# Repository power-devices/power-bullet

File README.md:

# Welcome to the Power Bullet electronics repository

I teach power electronics and I want to provide my students the best experience possible. This is the reason I created this project. I intend to allow people to produce power electronics devices at an extreme low cost. This board required 4 layers, but this is no problem today due to [JLCPCB](https://jlcpcb.com/) or other manufacturers.

So far, the project is divided into 3 pieces:

 1. Power supply: used to delivery power the other boards, it is compatible with mono-three phase up to 220 VAC
 2. Power bullet: a three phase h-bridge, simple as that
 3. Power brain F103: the main controller

# Disclaimer

I provide no warranty at all. Use it at your own risk!

# What will I find here?

You will find the design and production files. To edit the schematic/board you will need to install Kicad. I used version 7 to create this board.

# What can I do with this?

In this repository the board design and production files are stored. You are welcome to download/distribute it, use it, whatever.

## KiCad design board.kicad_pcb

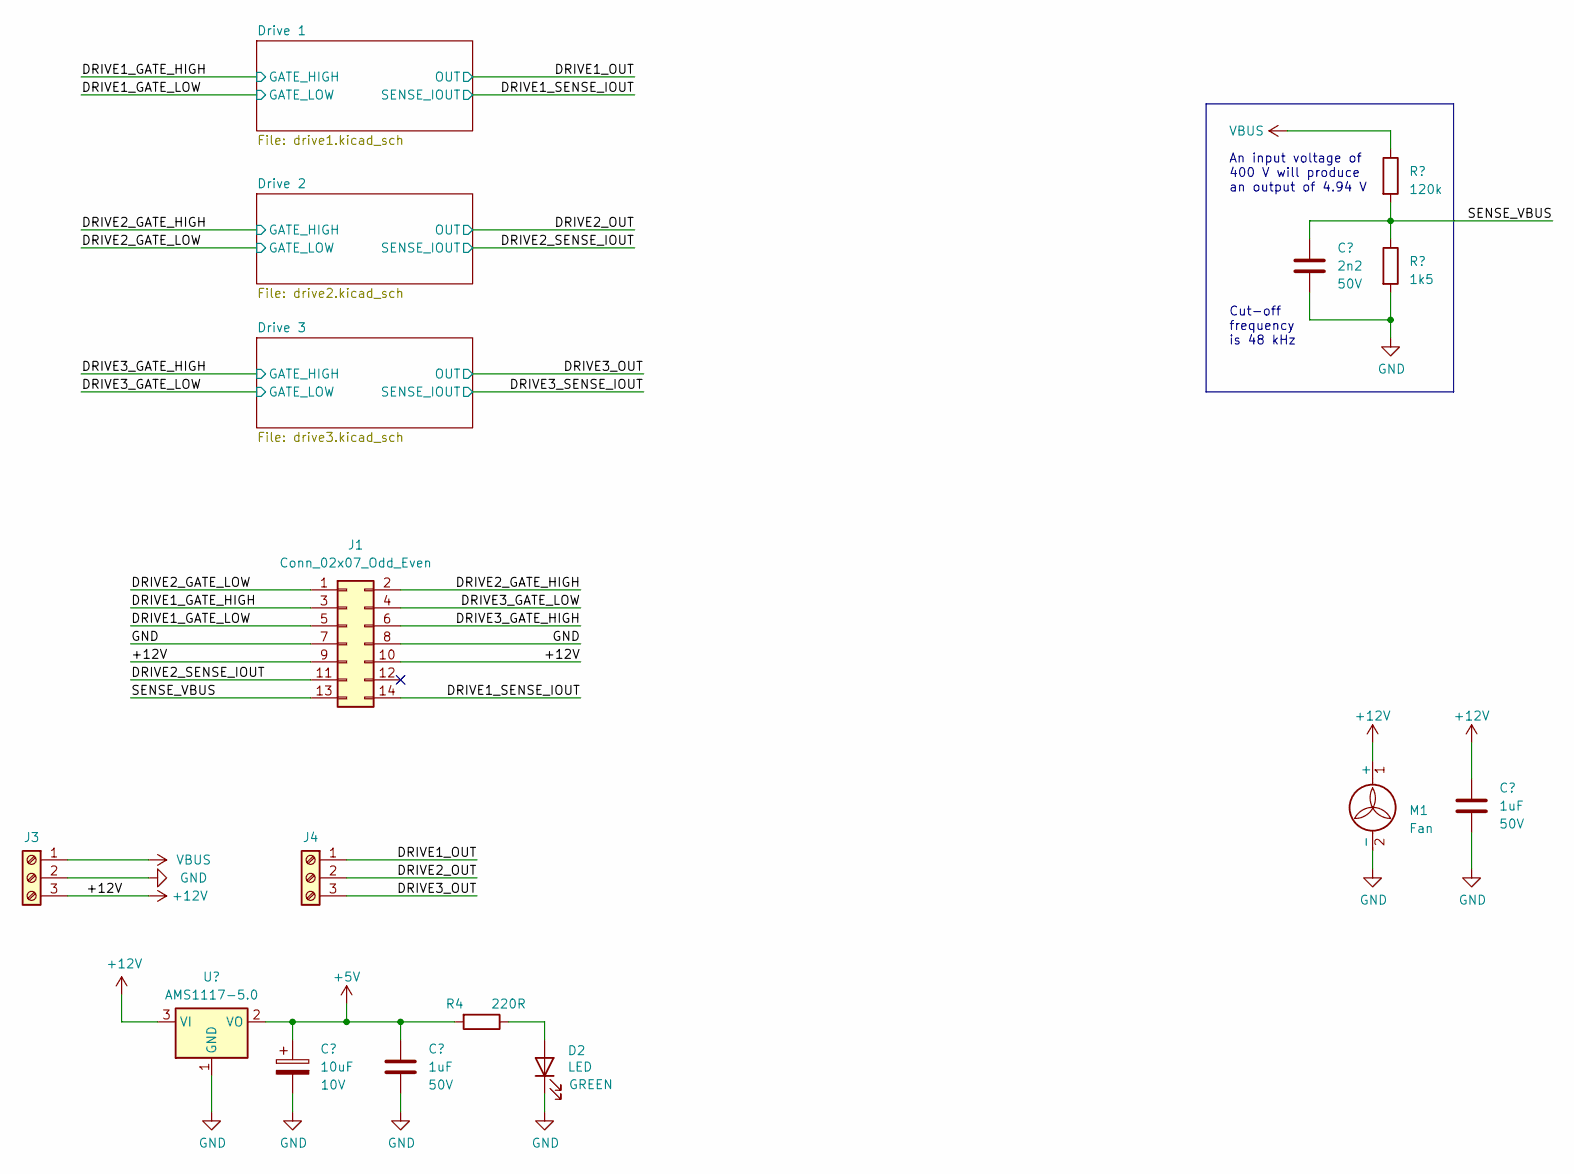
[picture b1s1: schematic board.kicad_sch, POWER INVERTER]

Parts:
C1, C5: 1uF; C_1206_3216Metric_Pad1.33x1.80mm_HandSolder; Voltage 50V
C2: 2n2; C_1206_3216Metric; Voltage 50V
C4: 10uF; CP_EIA-3216-18_Kemet-A; Voltage 10V
D2: LED; LED_1206_3216Metric_Pad1.42x1.75mm_HandSolder
J1: Conn_02x07_Odd_Even; IDC-Header_2x07_P2.54mm_Vertical
J3, J4: Screw_Terminal_01x03; TerminalBlock_Phoenix_MKDS-1,5-3_1x03_P5.00mm_Horizontal
M1: Fan; JST_XH_B2B-XH-A_1x02_P2.50mm_Vertical
R1: 120k; R_1206_3216Metric_Pad1.30x1.75mm_HandSolder
R2: 1k5; R_1206_3216Metric_Pad1.30x1.75mm_HandSolder
R4: 220R; R_1206_3216Metric_Pad1.30x1.75mm_HandSolder
U2: AMS1117-5.0; SOT-223-3_TabPin2

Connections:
+5V: C4.1, C5.1, R4.2, U2.2 (VO); also elsewhere on the board
+12V: C1.1, J1.9, J1.10, J3.3, M1.1 (+), U2.3 (VI); also elsewhere on the board
/DRIVE1_GATE_HIGH: J1.3; also elsewhere on the board
/DRIVE1_GATE_LOW: J1.5; also elsewhere on the board
/DRIVE1_OUT: J4.1; also elsewhere on the board
/DRIVE1_SENSE_IOUT: J1.14; also elsewhere on the board
/DRIVE2_GATE_HIGH: J1.2; also elsewhere on the board
/DRIVE2_GATE_LOW: J1.1; also elsewhere on the board
/DRIVE2_OUT: J4.2; also elsewhere on the board
/DRIVE2_SENSE_IOUT: J1.11; also elsewhere on the board
/DRIVE3_GATE_HIGH: J1.6; also elsewhere on the board
/DRIVE3_GATE_LOW: J1.4; also elsewhere on the board
/DRIVE3_OUT: J4.3; also elsewhere on the board
/SENSE_VBUS: C2.1, J1.13, R1.2, R2.1
GND: C1.2, C2.2, C4.2, C5.2, D2.1 (K), J1.7, J1.8, J3.2, M1.2 (-), R2.2, U2.1 (GND); also elsewhere on the board
unnamed: D2.2 (A), R4.1
VBUS: J3.1, R1.1; also elsewhere on the board

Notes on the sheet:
An input voltage of 400 V will produce an output of 4.94 V
Cut-off frequency is 48 kHz

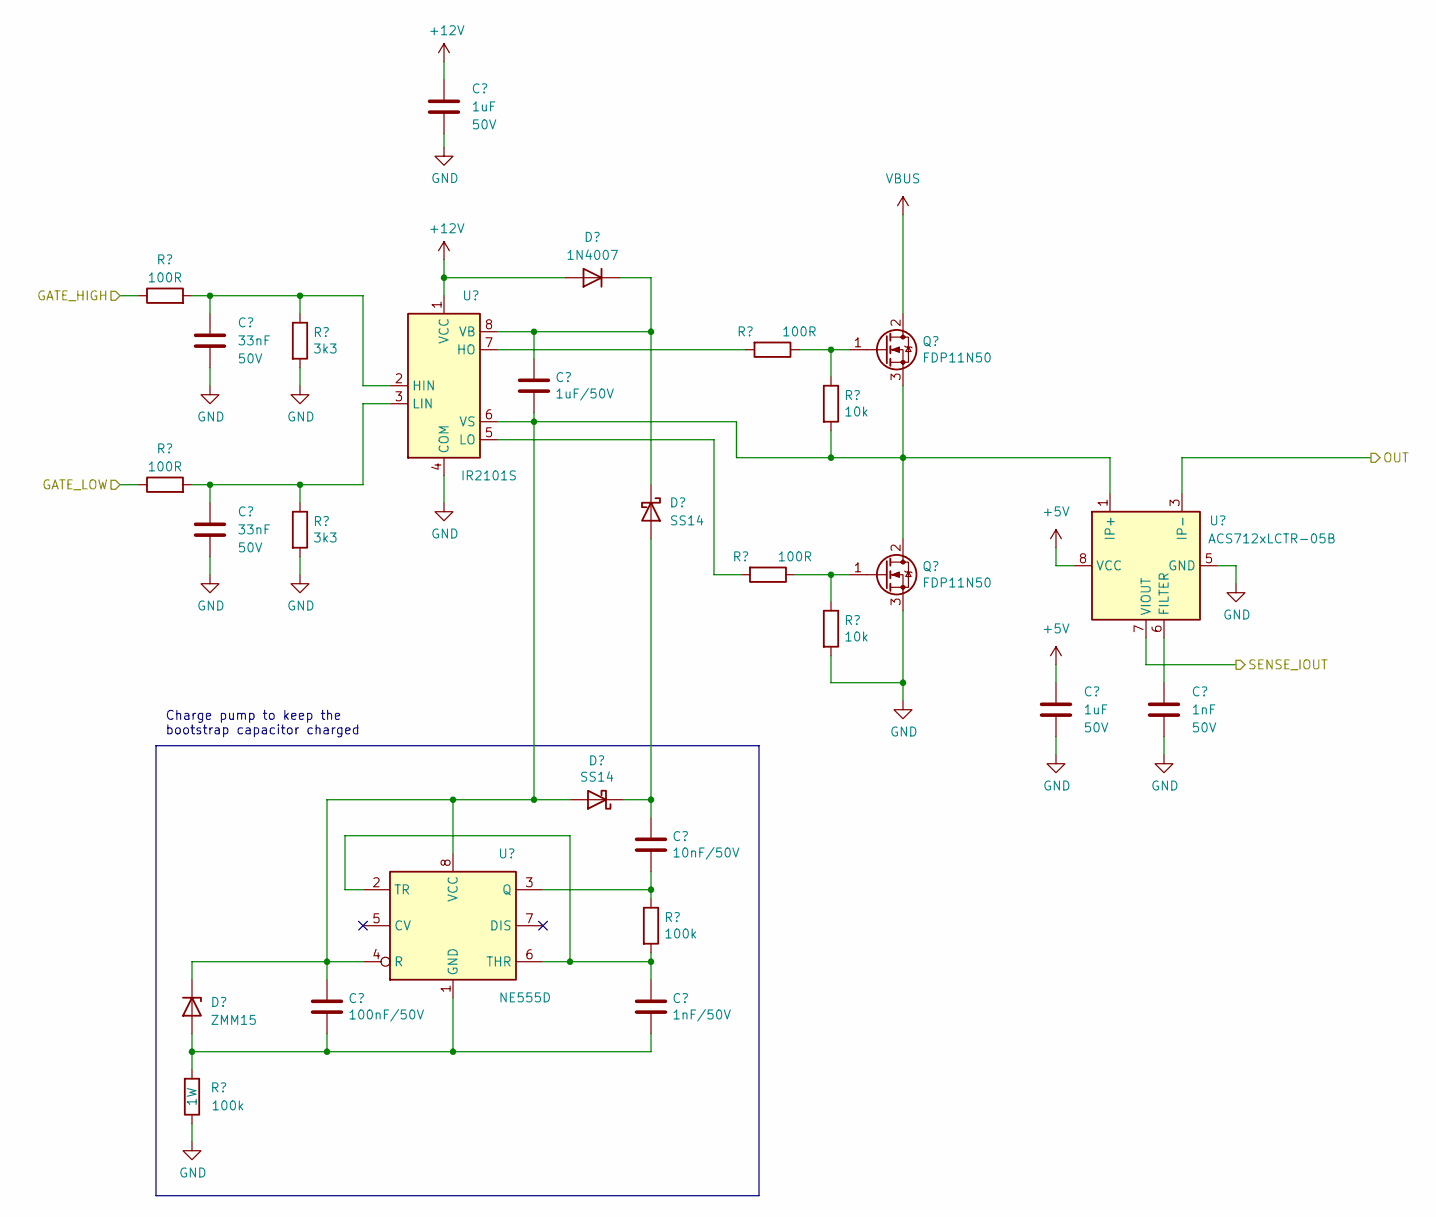
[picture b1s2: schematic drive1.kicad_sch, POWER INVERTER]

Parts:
C8, C14: 1uF; C_1206_3216Metric_Pad1.33x1.80mm_HandSolder; Voltage 50V
C10, C13: 33nF; C_1206_3216Metric; Voltage 50V
C11: 1uF/50V; C_1206_3216Metric_Pad1.33x1.80mm_HandSolder
C15: 1nF; C_1206_3216Metric_Pad1.33x1.80mm_HandSolder; Voltage 50V
C17: 10nF/50V; C_1206_3216Metric_Pad1.33x1.80mm_HandSolder
C18: 100nF/50V; C_1206_3216Metric_Pad1.33x1.80mm_HandSolder
C19: 1nF/50V; C_1206_3216Metric_Pad1.33x1.80mm_HandSolder
D3: 1N4007; D_SMA
D4, D5: SS14; D_SMA
D6: ZMM15; D_MiniMELF
Q1, Q2: FDP11N50; TO-220-3_Vertical
R5, R7, R9, R11: 100R; R_1206_3216Metric_Pad1.30x1.75mm_HandSolder
R6, R10: 3k3; R_1206_3216Metric_Pad1.30x1.75mm_HandSolder
R8, R12: 10k; R_1206_3216Metric_Pad1.30x1.75mm_HandSolder
R15: 100k; R_1206_3216Metric_Pad1.30x1.75mm_HandSolder
R16: 100k; R_1206_3216Metric
U3: IR2101S; SOIC-8_3.9x4.9mm_P1.27mm
U4: ACS712xLCTR-05B; SOIC-8_3.9x4.9mm_P1.27mm
U5: NE555D; SOIC-8_3.9x4.9mm_P1.27mm

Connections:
+5V: C14.1, U4.8 (VCC); also elsewhere on the board
+12V: C8.1, D3.2 (A), U3.1 (VCC); also elsewhere on the board
/DRIVE1_GATE_HIGH: R5.1; also elsewhere on the board
/DRIVE1_GATE_LOW: R9.1; also elsewhere on the board
/DRIVE1_OUT: U4.3 (IP-), U4.4 (IP-); also elsewhere on the board
/DRIVE1_SENSE_IOUT: U4.7 (VIOUT); also elsewhere on the board
GND: C8.2, C10.2, C13.2, C14.2, C15.2, Q2.3 (S), R6.2, R10.2, R12.2, R16.1, U3.4 (COM), U4.5 (GND); also elsewhere on the board
unnamed: C11.1, D3.1 (K), D4.1 (K), U3.8 (VB)
unnamed: C17.1, D4.2 (A), D5.1 (K)
unnamed: C11.2, C18.1, D5.2 (A), D6.1 (K), Q1.3 (S), Q2.2 (D), R8.2, U3.6 (VS), U4.1 (IP+), U4.2 (IP+), U5.4 (R), U5.8 (VCC)
unnamed: C18.2, C19.2, D6.2 (A), R16.2, U5.1 (GND)
unnamed: Q1.1 (G), R7.1, R8.1
unnamed: Q2.1 (G), R11.1, R12.1
unnamed: C10.1, R5.2, R6.1, U3.2 (HIN)
unnamed: R7.2, U3.7 (HO)
unnamed: C13.1, R9.2, R10.1, U3.3 (LIN)
unnamed: R11.2, U3.5 (LO)
unnamed: C15.1, U4.6 (FILTER)
unnamed: C17.2, R15.1, U5.3 (Q)
unnamed: C19.1, R15.2, U5.2 (TR), U5.6 (THR)
VBUS: Q1.2 (D); also elsewhere on the board

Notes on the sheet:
Charge pump to keep the bootstrap capacitor charged

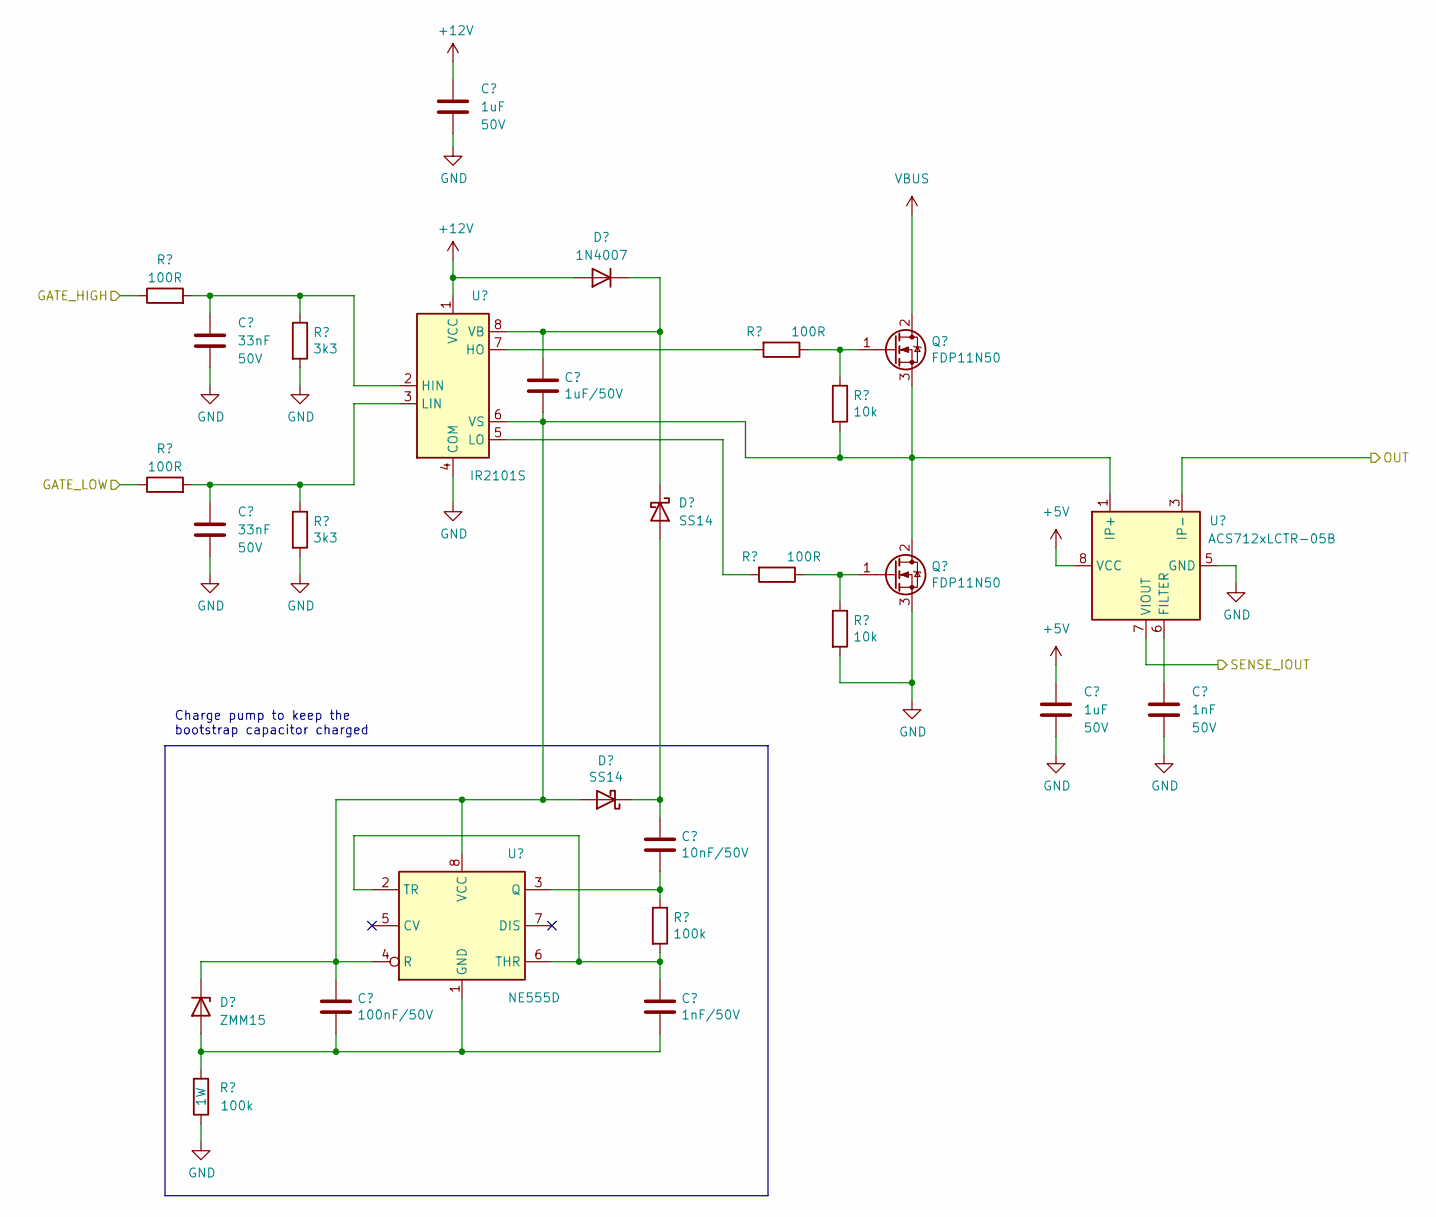
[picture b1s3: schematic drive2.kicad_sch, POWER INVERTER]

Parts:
C20, C26: 1uF; C_1206_3216Metric_Pad1.33x1.80mm_HandSolder; Voltage 50V
C22, C25: 33nF; C_1206_3216Metric; Voltage 50V
C23: 1uF/50V; C_1206_3216Metric_Pad1.33x1.80mm_HandSolder
C27: 1nF; C_1206_3216Metric_Pad1.33x1.80mm_HandSolder; Voltage 50V
C29: 10nF/50V; C_1206_3216Metric_Pad1.33x1.80mm_HandSolder
C30: 100nF/50V; C_1206_3216Metric_Pad1.33x1.80mm_HandSolder
C31: 1nF/50V; C_1206_3216Metric_Pad1.33x1.80mm_HandSolder
D7: 1N4007; D_SMA
D8, D9: SS14; D_SMA
D10: ZMM15; D_MiniMELF
Q3, Q4: FDP11N50; TO-220-3_Vertical
R17, R19, R21, R23: 100R; R_1206_3216Metric_Pad1.30x1.75mm_HandSolder
R18, R22: 3k3; R_1206_3216Metric_Pad1.30x1.75mm_HandSolder
R20, R24: 10k; R_1206_3216Metric_Pad1.30x1.75mm_HandSolder
R27, R28: 100k; R_1206_3216Metric_Pad1.30x1.75mm_HandSolder
U6: IR2101S; SOIC-8_3.9x4.9mm_P1.27mm
U7: ACS712xLCTR-05B; SOIC-8_3.9x4.9mm_P1.27mm
U8: NE555D; SOIC-8_3.9x4.9mm_P1.27mm

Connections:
+5V: C26.1, U7.8 (VCC); also elsewhere on the board
+12V: C20.1, D7.2 (A), U6.1 (VCC); also elsewhere on the board
/DRIVE2_GATE_HIGH: R17.1; also elsewhere on the board
/DRIVE2_GATE_LOW: R21.1; also elsewhere on the board
/DRIVE2_OUT: U7.3 (IP-), U7.4 (IP-); also elsewhere on the board
/DRIVE2_SENSE_IOUT: U7.7 (VIOUT); also elsewhere on the board
GND: C20.2, C22.2, C25.2, C26.2, C27.2, Q4.3 (S), R18.2, R22.2, R24.2, R28.1, U6.4 (COM), U7.5 (GND); also elsewhere on the board
unnamed: C23.1, D7.1 (K), D8.1 (K), U6.8 (VB)
unnamed: C29.1, D8.2 (A), D9.1 (K)
unnamed: C30.2, C31.2, D10.2 (A), R28.2, U8.1 (GND)
unnamed: C23.2, C30.1, D9.2 (A), D10.1 (K), Q3.3 (S), Q4.2 (D), R20.2, U6.6 (VS), U7.1 (IP+), U7.2 (IP+), U8.4 (R), U8.8 (VCC)
unnamed: Q3.1 (G), R19.1, R20.1
unnamed: Q4.1 (G), R23.1, R24.1
unnamed: C22.1, R17.2, R18.1, U6.2 (HIN)
unnamed: R19.2, U6.7 (HO)
unnamed: C25.1, R21.2, R22.1, U6.3 (LIN)
unnamed: R23.2, U6.5 (LO)
unnamed: C27.1, U7.6 (FILTER)
unnamed: C29.2, R27.1, U8.3 (Q)
unnamed: C31.1, R27.2, U8.2 (TR), U8.6 (THR)
VBUS: Q3.2 (D); also elsewhere on the board

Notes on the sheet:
Charge pump to keep the bootstrap capacitor charged

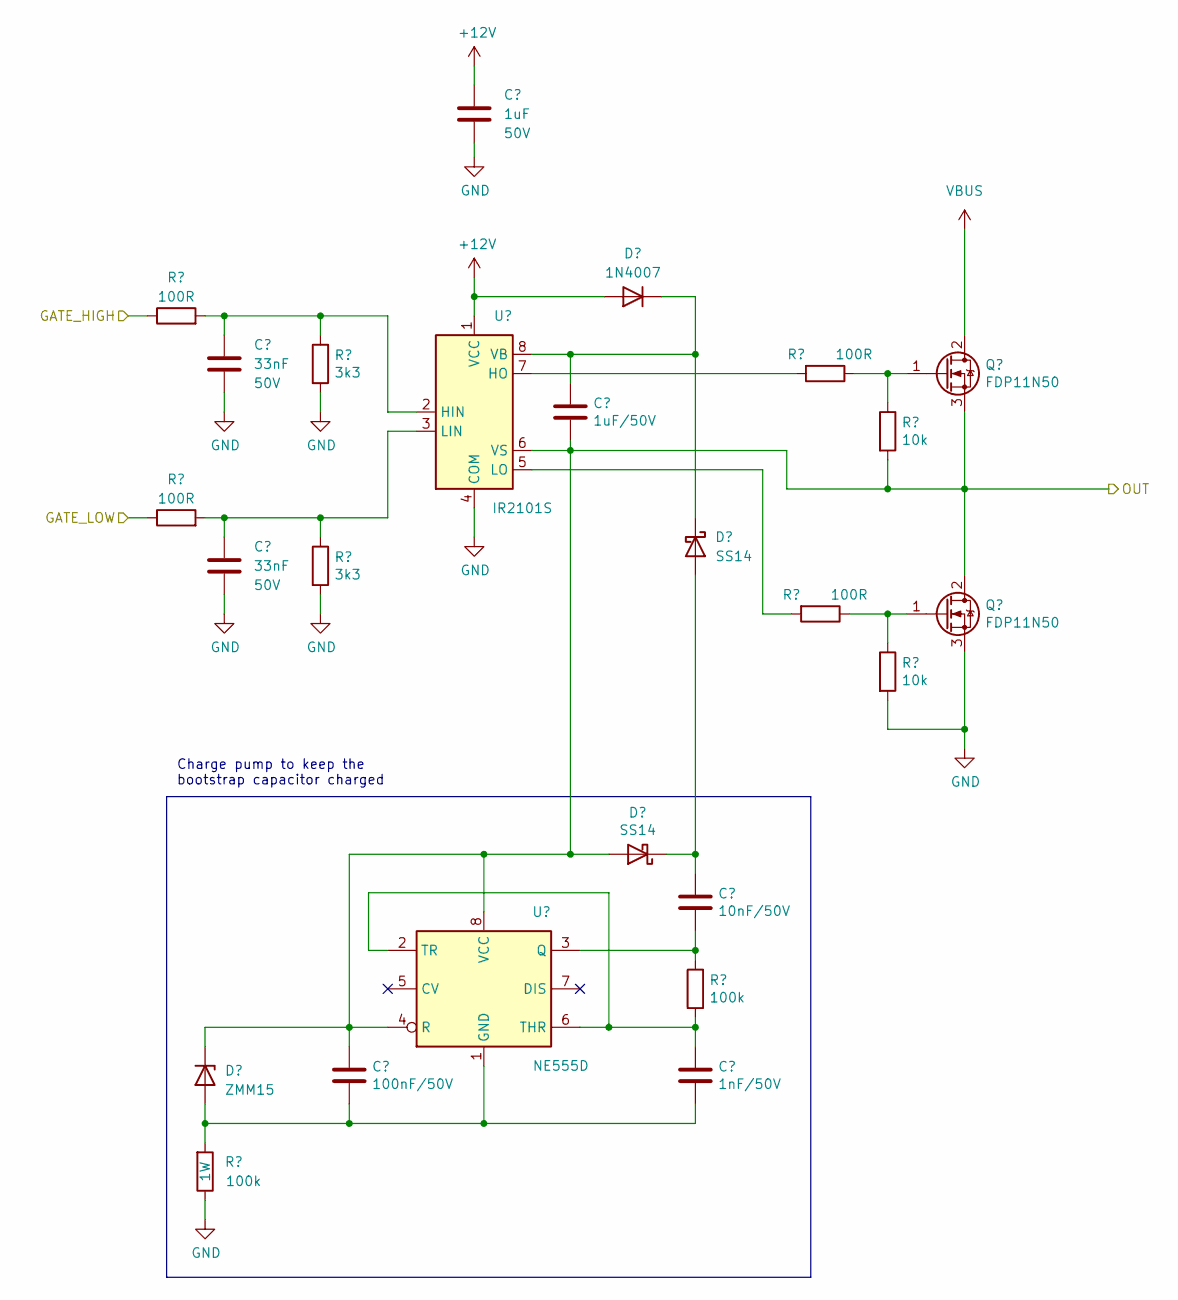
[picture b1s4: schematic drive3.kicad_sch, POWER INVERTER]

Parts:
C32: 1uF; C_1206_3216Metric_Pad1.33x1.80mm_HandSolder; Voltage 50V
C34, C37: 33nF; C_1206_3216Metric; Voltage 50V
C35: 1uF/50V; C_1206_3216Metric_Pad1.33x1.80mm_HandSolder
C41: 10nF/50V; C_1206_3216Metric_Pad1.33x1.80mm_HandSolder
C42: 100nF/50V; C_1206_3216Metric_Pad1.33x1.80mm_HandSolder
C43: 1nF/50V; C_1206_3216Metric_Pad1.33x1.80mm_HandSolder
D11: 1N4007; D_SMA
D12, D13: SS14; D_SMA
D14: ZMM15; D_MiniMELF
Q5, Q6: FDP11N50; TO-220-3_Vertical
R29, R31, R33, R35: 100R; R_1206_3216Metric_Pad1.30x1.75mm_HandSolder
R30, R34: 3k3; R_1206_3216Metric_Pad1.30x1.75mm_HandSolder
R32, R36: 10k; R_1206_3216Metric_Pad1.30x1.75mm_HandSolder
R39, R40: 100k; R_1206_3216Metric_Pad1.30x1.75mm_HandSolder
U9: IR2101S; SOIC-8_3.9x4.9mm_P1.27mm
U11: NE555D; SOIC-8_3.9x4.9mm_P1.27mm

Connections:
+12V: C32.1, D11.2 (A), U9.1 (VCC); also elsewhere on the board
/DRIVE3_GATE_HIGH: R29.1; also elsewhere on the board
/DRIVE3_GATE_LOW: R33.1; also elsewhere on the board
/DRIVE3_OUT: C35.2, C42.1, D13.2 (A), D14.1 (K), Q5.3 (S), Q6.2 (D), R32.2, U9.6 (VS), U11.4 (R), U11.8 (VCC); also elsewhere on the board
GND: C32.2, C34.2, C37.2, Q6.3 (S), R30.2, R34.2, R36.2, R40.1, U9.4 (COM); also elsewhere on the board
unnamed: C35.1, D11.1 (K), D12.1 (K), U9.8 (VB)
unnamed: C41.1, D12.2 (A), D13.1 (K)
unnamed: C42.2, C43.2, D14.2 (A), R40.2, U11.1 (GND)
unnamed: Q5.1 (G), R31.1, R32.1
unnamed: Q6.1 (G), R35.1, R36.1
unnamed: C34.1, R29.2, R30.1, U9.2 (HIN)
unnamed: R31.2, U9.7 (HO)
unnamed: C37.1, R33.2, R34.1, U9.3 (LIN)
unnamed: R35.2, U9.5 (LO)
unnamed: C41.2, R39.1, U11.3 (Q)
unnamed: C43.1, R39.2, U11.2 (TR), U11.6 (THR)
VBUS: Q5.2 (D); also elsewhere on the board

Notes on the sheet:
Charge pump to keep the bootstrap capacitor charged

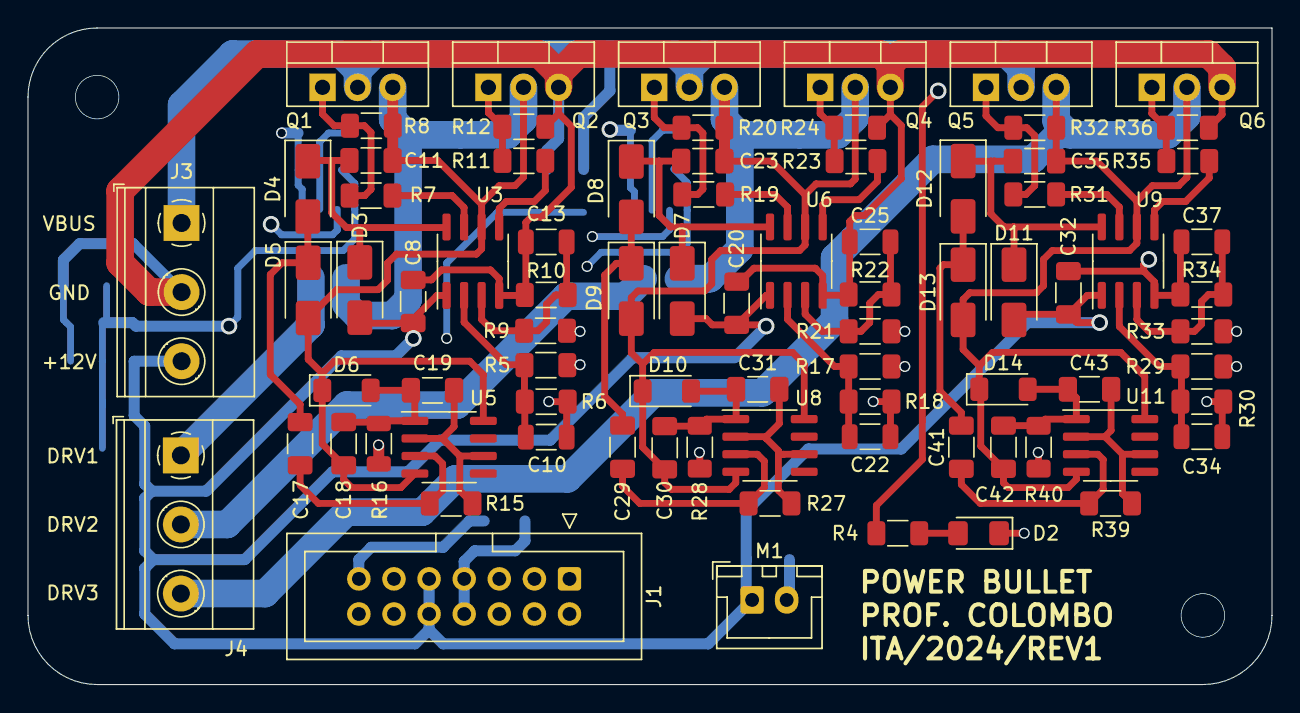
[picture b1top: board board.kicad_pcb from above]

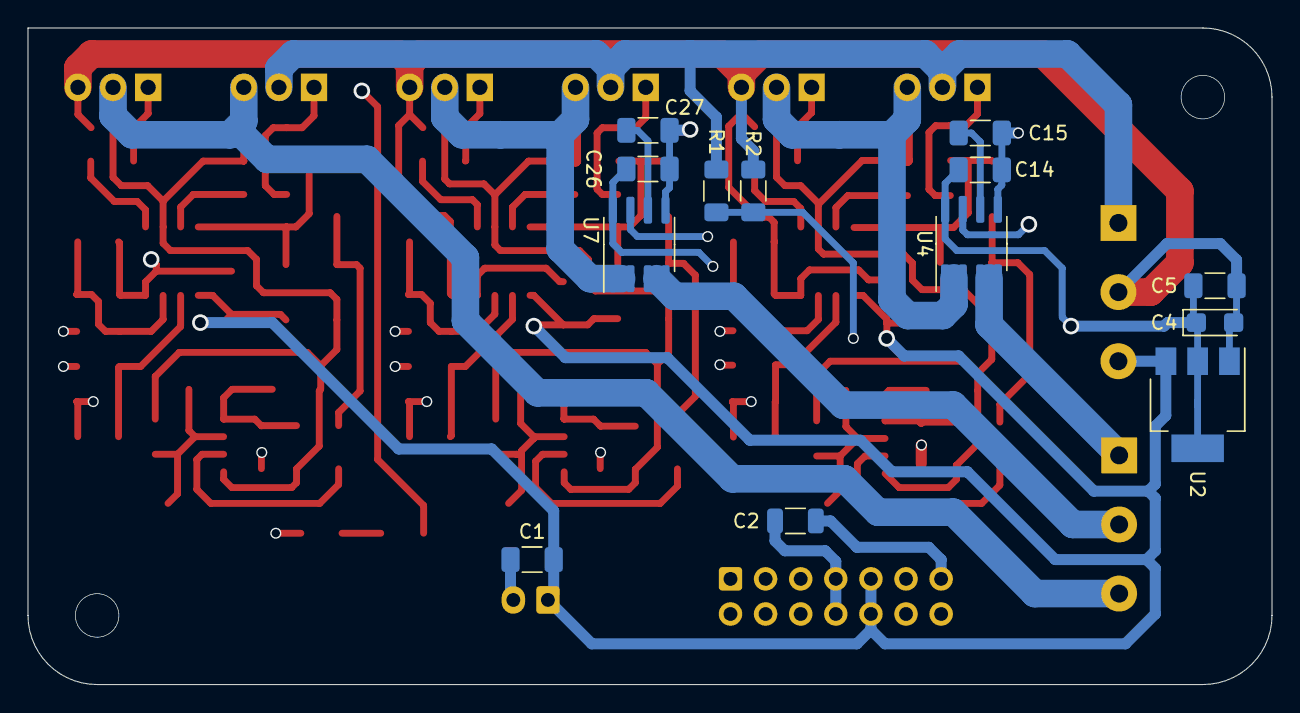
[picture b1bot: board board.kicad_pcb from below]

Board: 4 copper layers, 90.0 x 47.5 mm, 94 parts (13 on the bottom side), 54 nets.

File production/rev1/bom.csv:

Designator,Footprint,Quantity,Value,LCSC Part #
"C1, C14, C20, C26, C32, C5, C8",1206,7,1uF,
"C10, C13, C22, C25, C34, C37",1206,6,33nF,
"C11, C23, C35",1206,3,1uF/50V,
"C15, C27",1206,2,1nF,
"C17, C29, C41",1206,3,10nF/50V,
"C18, C30, C42",1206,3,100nF/50V,
"C19, C31, C43",1206,3,1nF/50V,
C2,1206,1,2n2,
C4,CP_EIA-3216-18_Kemet-A,1,10uF,
"D10, D14, D6",D_MiniMELF,3,ZMM15,
"D11, D3, D7",D_SMA,3,1N4007,
"D12, D13, D4, D5, D8, D9",D_SMA,6,SS14,
D2,1206,1,LED,
J1,IDC-Header_2x07_P2.54mm_Vertical,1,Conn_02x07_Odd_Even,
"J3, J4","TerminalBlock_Phoenix_MKDS-1,5-3_1x03_P5.00mm_Horizontal",2,Screw_Terminal_01x03,
M1,JST_XH_B2B-XH-A_1x02_P2.50mm_Vertical,1,Fan,
"Q1, Q2, Q3, Q4, Q5, Q6",TO-220-3_Vertical,6,FDP11N50,
R1,1206,1,120k,
"R10, R18, R22, R30, R34, R6",1206,6,3k3,
"R11, R17, R19, R21, R23, R29, R31, R33, R35, R5, R7, R9",1206,12,100R,
"R12, R20, R24, R32, R36, R8",1206,6,10k,
"R15, R16, R27, R28, R39, R40",1206,6,100k,
R2,1206,1,1k5,
R4,1206,1,220R,
"U11, U5, U8",SOIC-8_3.9x4.9mm_P1.27mm,3,NE555D,
U2,SOT-223-3_TabPin2,1,AMS1117-5.0,
"U3, U6, U9",SOIC-8_3.9x4.9mm_P1.27mm,3,IR2101S,
"U4, U7",SOIC-8_3.9x4.9mm_P1.27mm,2,ACS712xLCTR-05B,

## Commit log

2023-11-22 Added the REV1 files.
